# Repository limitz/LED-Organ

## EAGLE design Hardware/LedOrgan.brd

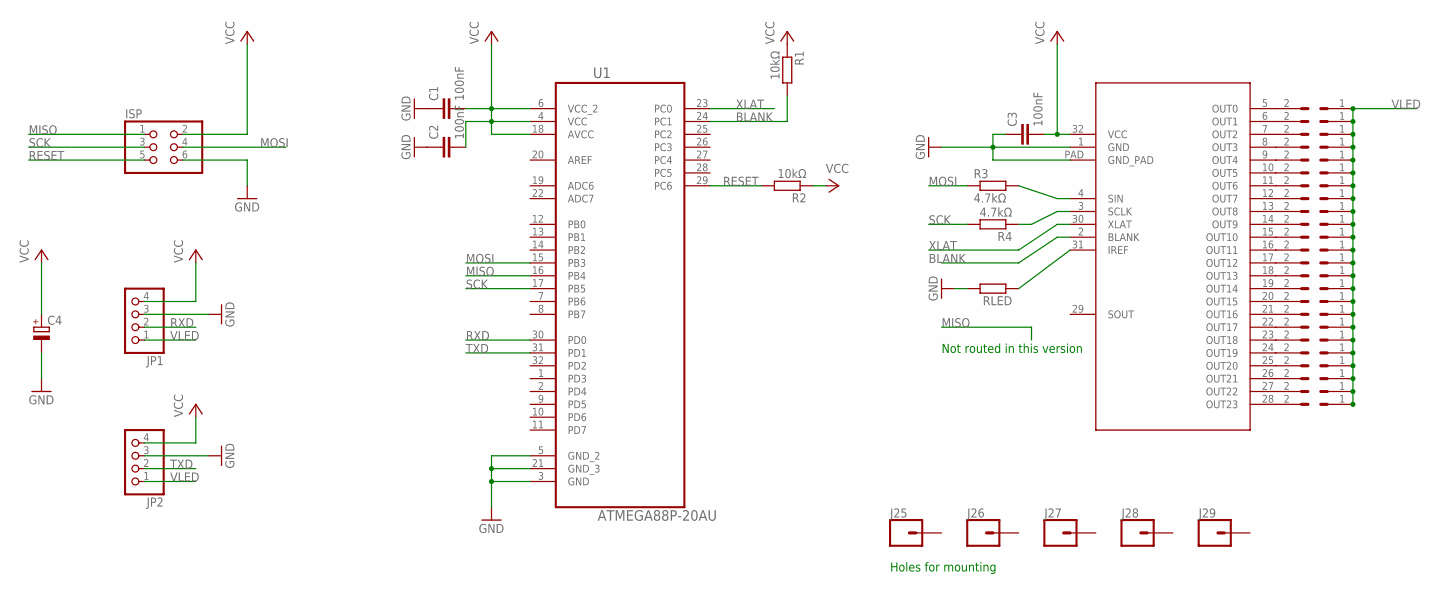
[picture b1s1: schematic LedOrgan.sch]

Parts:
C1, C2, C3: 100nF; C0402
C4: CPOL-EUE2.5-5; E2,5-5
ISP: PINHD-2X3; 2X03
J1, J2, J3, J4, J5, J6, J7, J8, J9, J10, J11, J12, J13, J14, J15, J16, J17, J18, J19, J20, J21, J22, J23, J24: CONN_021X02_NO_SILK; 1X02_NO_SILK
J25, J26, J27, J28, J29: CONN_01PTH_NO_SILK_YES_STOP; 1X01_NO_SILK
JP1, JP2: PINHD-1X4; 1X04
R1, R2: 10kΩ; M0805
R3, R4: 4.7kΩ; R0402
RLED: R-EU_M0805; M0805
U1: ATMEGA88P-20AU; QFP80P900X900X120-32N
U$2: TLC5947; TSSOP-32

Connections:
BLANK: R1.2, U1.24 (PC1), U$2.2 (BLANK)
GND: C1.1, C2.1, C3.1, C4.-, ISP.6, JP1.3, JP2.3, RLED.2, U1.3 (GND), U1.5 (GND_2), U1.21 (GND_3), U$2.1 (GND), U$2.PAD (GND_PAD)
MISO: ISP.1, U1.16 (PB4)
MOSI: ISP.4, R3.1, U1.15 (PB3)
unnamed: RLED.1, U$2.31 (IREF)
unnamed: R4.1, U$2.3 (SCLK)
unnamed: R3.2, U$2.4 (SIN)
unnamed: J1.2, U$2.5 (OUT0)
unnamed: J2.2, U$2.6 (OUT1)
unnamed: J3.2, U$2.7 (OUT2)
unnamed: J4.2, U$2.8 (OUT3)
unnamed: J5.2, U$2.9 (OUT4)
unnamed: J6.2, U$2.10 (OUT5)
unnamed: J7.2, U$2.11 (OUT6)
unnamed: J8.2, U$2.12 (OUT7)
unnamed: J9.2, U$2.13 (OUT8)
unnamed: J10.2, U$2.14 (OUT9)
unnamed: J11.2, U$2.15 (OUT10)
unnamed: J12.2, U$2.16 (OUT11)
unnamed: J13.2, U$2.17 (OUT12)
unnamed: J14.2, U$2.18 (OUT13)
unnamed: J15.2, U$2.19 (OUT14)
unnamed: J16.2, U$2.20 (OUT15)
unnamed: J17.2, U$2.21 (OUT16)
unnamed: J18.2, U$2.22 (OUT17)
unnamed: J19.2, U$2.23 (OUT18)
unnamed: J20.2, U$2.24 (OUT19)
unnamed: J21.2, U$2.25 (OUT20)
unnamed: J22.2, U$2.26 (OUT21)
unnamed: J23.2, U$2.27 (OUT22)
unnamed: J24.2, U$2.28 (OUT23)
RESET: ISP.5, R2.2, U1.29 (PC6)
RXD: JP1.2, U1.30 (PD0)
SCK: ISP.3, R4.2, U1.17 (PB5)
TXD: JP2.2, U1.31 (PD1)
VCC: C1.2, C2.2, C3.2, C4.+, ISP.2, JP1.4, JP2.4, R1.1, R2.1, U1.4 (VCC), U1.6 (VCC_2), U1.18 (AVCC), U$2.32 (VCC)
VLED: J1.1, J2.1, J3.1, J4.1, J5.1, J6.1, J7.1, J8.1, J9.1, J10.1, J11.1, J12.1, J13.1, J14.1, J15.1, J16.1, J17.1, J18.1, J19.1, J20.1, J21.1, J22.1, J23.1, J24.1, JP1.1, JP2.1
XLAT: U1.23 (PC0), U$2.30 (XLAT)

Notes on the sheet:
Not routed in this version
Holes for mounting

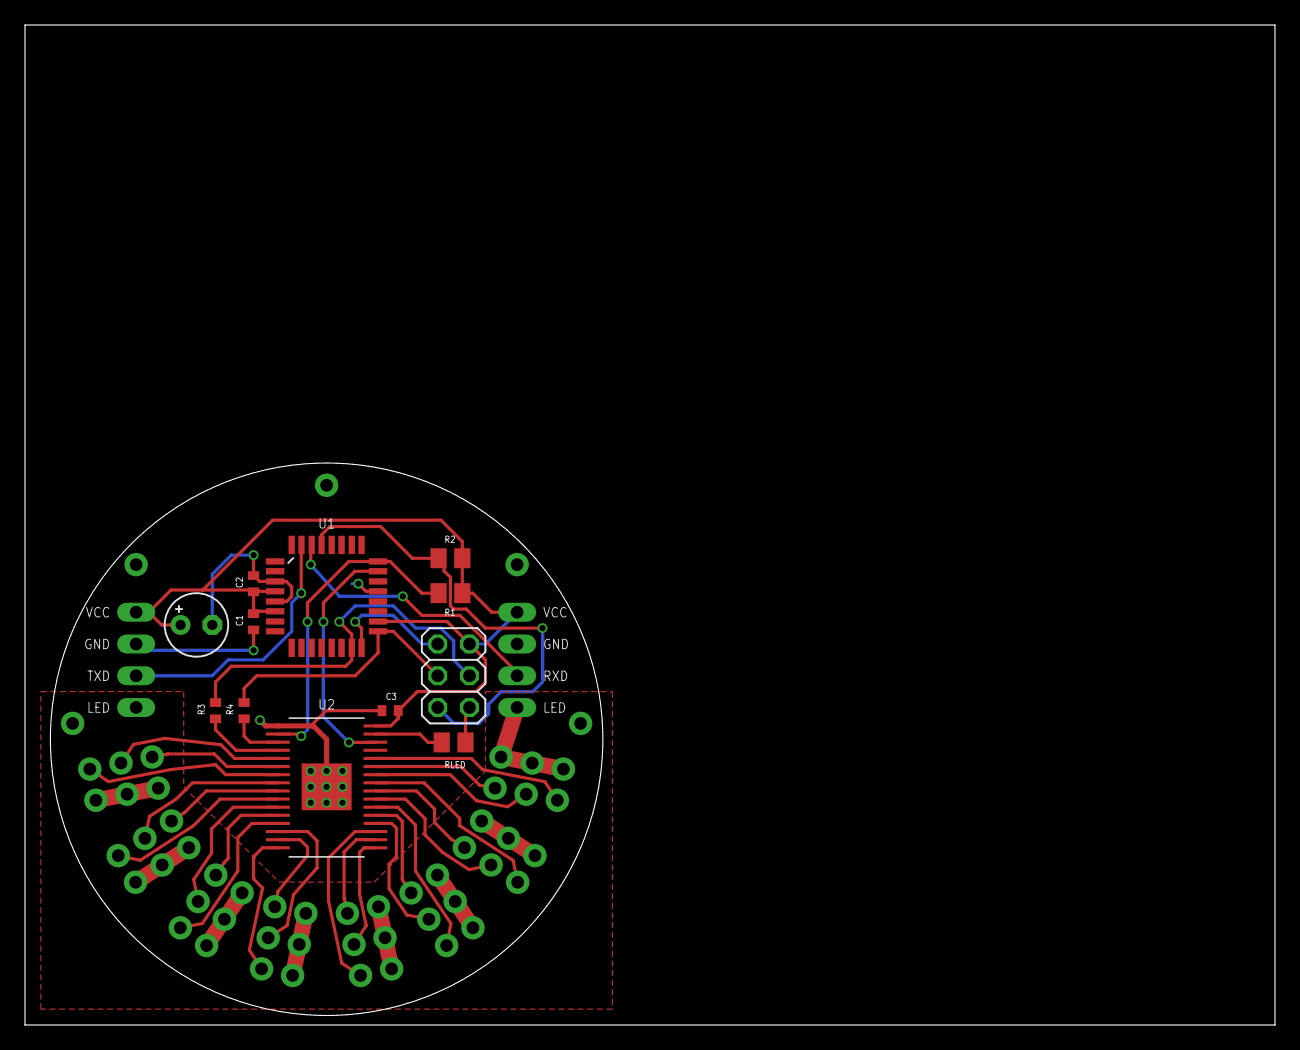
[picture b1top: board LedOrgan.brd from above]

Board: 2 copper layers, 100.0 x 80.0 mm, 43 parts (0 on the bottom side), 38 nets.

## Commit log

2018-11-05 Initial commit, untested.

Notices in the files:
parts and their libraries:
SparkFun-Connectors: Licensing: Creative Commons ShareAlike 4.0 International - https://creativecommons.org/licenses/by-sa/4.0
